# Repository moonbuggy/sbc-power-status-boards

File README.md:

# Single Board Computer Power and LED Status Boards
KiCad files for a couple of PCBs that are useful with single board computers, to be built on stripboard.

This has been developed in the context of Banana Pi M2 Ultra and M3 devices, but will apply to similar devices. Obviously not all single board computers will have batteries, so the status LED may be less useful in many cases. The GPIO pin arrangement should be identical for many devices, but it would be worth confirming the pin numbers specified here are appropriate.

## Power Distribution Board
As well as splitting power to various components, accept a PWM signal from the device's GPIO (via an optocoupler) to switch a MOSFET and control a fan's speed.

The PWM bypass jumper can be omitted if you're confident the device's PWM function works. Conversely, the MOSFET and optocoupler can be omitted if there's no fan or running a fan at full speed whenever this board is powered is acceptable.

The `LED power` connector on this board will indicate whenever this board is powered, but is superseded by the LED status board for more advanced signalling of the power status.

### Software
I'm currently not confident my SBC's PWM function works. For the time being it's easiest to just use the GPIO to switch the fan all the way on or off, with no speed control.

The advantage of this over using the bypass jumper is that the fan only runs when the BPi is switched on. The bypass jumper runs the fan whenever the enclosure is connected to power, regardless of whether the BPi itself is on.

Using GPIO pin 13 (BCM 277) is convenient because there's an adjacent GND pin, so both connections are made with a single 1x2 jumper housing.

Configuring systemd to start the fan early in the init process looks like this:

```sh
sudo sh -c "cat << EOF > /etc/systemd/system/cooling-fan.service
[Unit]
Description=Enable cooling fan
Before=basic.target
After=local-fs.target sysinit.target
DefaultDependencies=no

[Service]
Type=oneshot
ExecStart=gpioset 0 277=1
ExecStop=gpioset 0 277=0
RemainAfterExit=yes

[Install]
WantedBy=basic.target
EOF"

sudo systemctl daemon-reload
sudo systemctl enable cooling-fan.service
```

## LED Status Board
A bi-colour LED connected to the GPIO can give useful status information.

The 5V pins on the GPIO are always powered when external power is connected, but the 3V3 pins are only powered when the device is turned on. The 3V3 pins are powered whether running off external power or battery. Using an AND gate (in this case an optocoupler) results in a LED that is only lit when the BPi is on and running on external power (and off when running on battery).

A general GPIO pin can be set high by systemd once booted, giving a "booted/ready" indication by directly powering the other colour in the LED.

It's convenient to use GPIO headers pins 4 (5V), 6 (GND), 17 (3V3) and 18 (GPIO 24, BCM 250). This leaves the I2C pins free and allows a PCB with female connectors to plug directly into the GPIO header with enough spacing between the pins for a robust connection.

Using a red/blue LED, this gives a unique identification for all scenarios except booting from battery:

| State | external | battery
| --- | --- | ---
| off | - | -
| booting | red | -
| booted | purple | blue

### Resistor selection
The values for resistors in these diagrams are chosen for the specific LED colour they'll be powering. The fixed series resistors before the trimpots are for protection, to prevent accidentally blowing LEDs or something on the SBC by winding a trimpot all the way to zero. If you're not using a blue LED on that channel, the 20ohm value in the schematic may be too low for that purpose.

The trimpots are solely for brightness adjustment and balancing the two colours when both are lit. They can be omitted in favour of fixed resistors if that's not a concern.

### Software
To make the boot LED service start after everything else has started, create a target that is reached after multi-user.target and then start the service at that point.

#### /etc/systemd/system/booted.target
```ini
[Unit]
Description=System is booted and ready (for toggling status LED)
Requires=multi-user.target
After=multi-user.target
AllowIsolate=yes
```

#### /etc/systemd/system/boot-led.service
```ini
[Unit]
Description='booted' status indicator LED
After=multi-user.target

[Service]
Type=oneshot
ExecStart=gpioset 0 250=1
ExecStop=gpioset 0 250=0
RemainAfterExit=yes

[Install]
WantedBy=booted.target
```

Finally, to enable the target and unit:
```sh
sudo mkdir /etc/systemd/system/booted.target.wants
sudo ln -s /etc/systemd/system/boot-led.service /etc/systemd/system/booted.target.wants/boot-led.service
sudo systemctl daemon-reload
sudo systemctl enable boot-led
sudo systemctl set-default booted.target
```

#### /usr/bin/bootled.sh
A shell script can also toggle the 'booted' LED:
```sh
#! /bin/sh

GPIO_bus="0"
GPIO_pin="250"

indication="$(echo ${1:-on} | tr '[:upper:]' '[:lower:]')"

case ${indication} in
        "on")
                gpioset ${GPIO_bus} ${GPIO_pin}=1
                ;;
        "off")
                gpioset ${GPIO_bus} ${GPIO_pin}=0
                ;;
        *)
                echo "Error: unknown state '${indication}'. Accepts 'on' or 'off'."
                exit 1
                ;;
esac
```

## Links
*   <https://github.com/moonbuggy/sbc-os-images>

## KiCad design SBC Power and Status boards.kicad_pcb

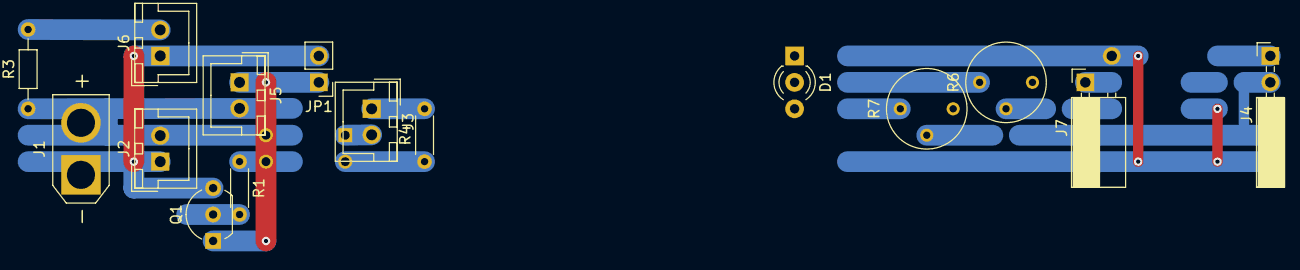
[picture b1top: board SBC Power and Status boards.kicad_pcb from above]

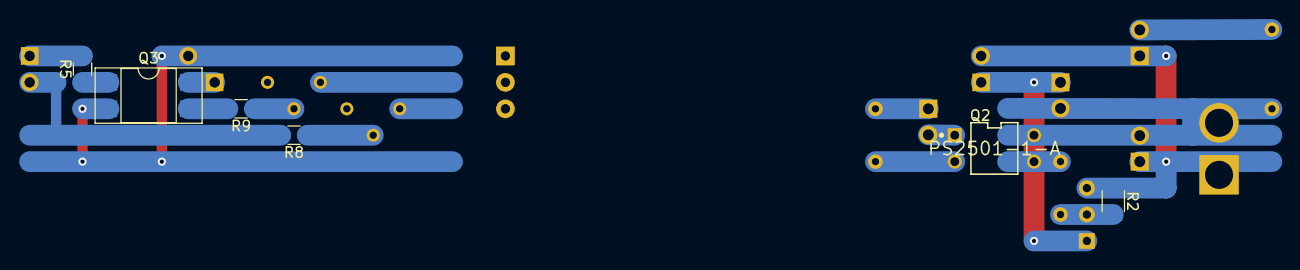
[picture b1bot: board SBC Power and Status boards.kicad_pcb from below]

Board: 2 copper layers, 21 parts (6 on the bottom side), 19 nets.

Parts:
D1: LED_Dual_ACA; LED_D3.0mm-3
J1: Power In; AMASS_XT30U-M_1x02_P5.0mm_Vertical
J2: BPi Power; JST_XH_B02B-XH-A_02x2.50mm_Straight
J3: BPi Signal; JST_XH_B02B-XH-A_02x2.50mm_Straight
J4: Conn_02x01_Female; Socket_Strip_Angled_2x01_Pitch2.54mm
J5: Fan Power; JST_XH_B02B-XH-A_02x2.50mm_Straight
J6: LED Power; JST_XH_B02B-XH-A_02x2.50mm_Straight
J7: Conn_01x02_Female; Socket_Strip_Angled_1x02_Pitch2.54mm-offset-pad-other
JP1: Jumper; Pin_Header_Straight_1x02_Pitch2.54mm
Q1: BS170; TO-92_Inline_Wide
Q2: PS2501-1-A; Renesas-PS2501-1-A-MFG
Q3: PS2501-1-A; DIP-4_W7.62mm_SMDSocket_SmallPads
R1: 47R; R_Axial_DIN0204_L3.6mm_D1.6mm_P5.08mm_Horizontal
R2: 1k; R_1206
R3: 1k5; R_Axial_DIN0204_L3.6mm_D1.6mm_P7.62mm_Horizontal
R4: 270R; R_Axial_DIN0204_L3.6mm_D1.6mm_P5.08mm_Horizontal
R5: 360R; R_0805
R6, R7: 2k; Potentiometer_Trimmer_Bourns_3339P_Horizontal
R8: 20R; R_0805
R9: 150R; R_0805

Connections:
+5V: J1.2, J2.2, J5.2, Q2.4, R3.1
GND: J1.1, J2.1, J6.1, JP1.2, Q1.3, R2.1
unnamed: D1.1, R6.3
unnamed: D1.2, J7.2, Q3.2
unnamed: D1.3, R7.3
unnamed: J3.1, R4.2
unnamed: J3.2, Q2.1
unnamed: J4.1, R5.2
unnamed: J4.2, R8.2
unnamed: J5.1, JP1.1, Q1.1
unnamed: J6.2, R3.2
unnamed: J7.1, Q3.4
unnamed: Q1.2, R1.2, R2.2
unnamed: Q2.2, R4.1
unnamed: Q2.3, R1.1
unnamed: Q3.1, R5.1
unnamed: Q3.3, R9.2
unnamed: R6.2, R9.1
unnamed: R7.2, R8.1
